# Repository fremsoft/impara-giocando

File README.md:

# impara-giocando

In questa directory verrà caricato tutto il materiale didattico che servirà per seguire meglio i laboratori di meccatronica «impara giocando»

La playlist completa è disponibile in abbonamento a questo link: [Laboratori di Meccatronica](https://www.youtube.com/playlist?list=PLxAafib4pWc7ZTqss_0A76ByotfsSOVeD)

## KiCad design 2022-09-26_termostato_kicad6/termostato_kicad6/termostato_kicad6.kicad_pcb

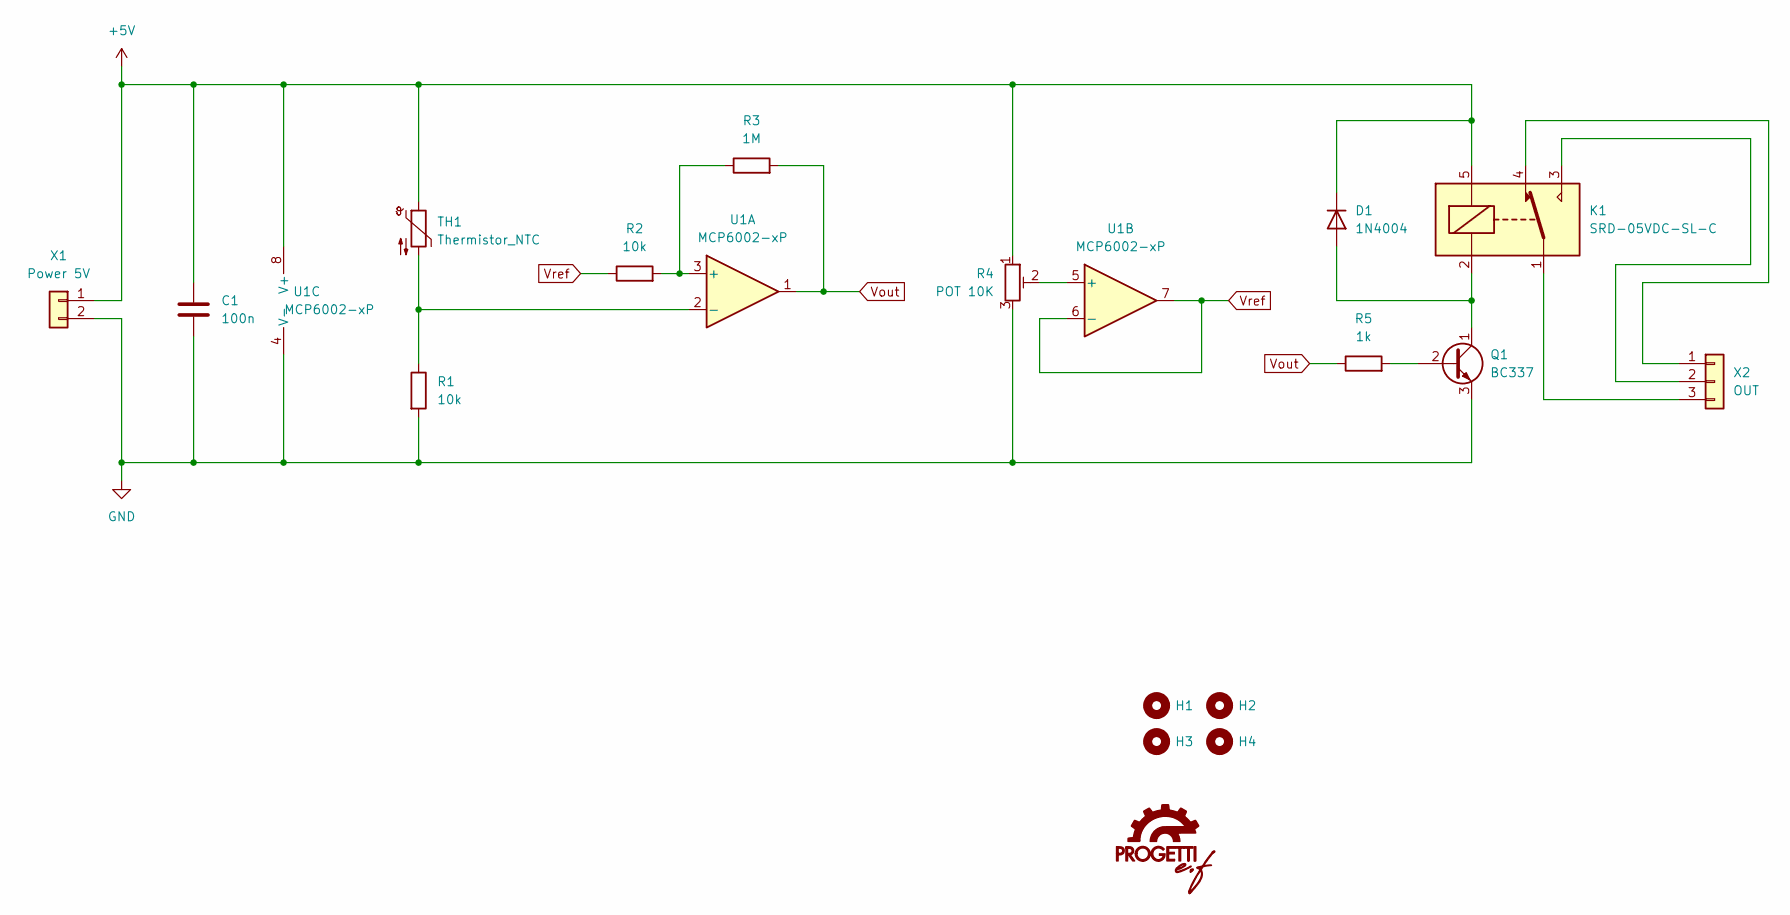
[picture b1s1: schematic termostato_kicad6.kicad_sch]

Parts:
C1: 100n; C_Disc_D7.5mm_W2.5mm_P5.00mm
D1: 1N4004; D_A-405_P10.16mm_Horizontal
H1, H2, H3, H4: MountingHole; MountingHole_4.3mm_M4
K1: SRD-05VDC-SL-C; Relay_SPDT_SANYOU_SRD_Series_Form_C
Q1: BC337; TO-92L_Inline_Wide
R1, R2: 10k; R_Axial_DIN0207_L6.3mm_D2.5mm_P10.16mm_Horizontal
R3: 1M; R_Axial_DIN0207_L6.3mm_D2.5mm_P10.16mm_Horizontal
R4: POT 10K; Potentiometer_Alps_RK163_Single_Horizontal
R5: 1k; R_Axial_DIN0207_L6.3mm_D2.5mm_P10.16mm_Horizontal
TH1: Thermistor_NTC; C_Rect_L4.6mm_W3.0mm_P2.50mm_MKS02_FKP02
U1: MCP6002-xP; DIP-8_W7.62mm_LongPads
X1: Power 5V; PhoenixContact_MSTBA_2,5_2-G-5,08_1x02_P5.08mm_Horizontal
X2: OUT; PhoenixContact_MSTBA_2,5_3-G-5,08_1x03_P5.08mm_Horizontal

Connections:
+5V: C1.1, D1.1 (K), K1.5, R4.1, TH1.1, U1.8 (V+), X1.1
GND: C1.2, Q1.3 (E), R1.2, R4.3, U1.4 (V-), X1.2
unnamed: D1.2 (A), K1.2, Q1.1 (C)
unnamed: K1.1, X2.3
unnamed: K1.3, X2.2
unnamed: K1.4, X2.1
unnamed: Q1.2 (B), R5.2
unnamed: R1.1, TH1.2, U1.2 (-)
unnamed: R2.2, R3.1, U1.3 (+)
unnamed: R4.2, U1.5 (+)
Vout: R3.2, R5.1, U1.1
Vref: R2.1, U1.6 (-), U1.7

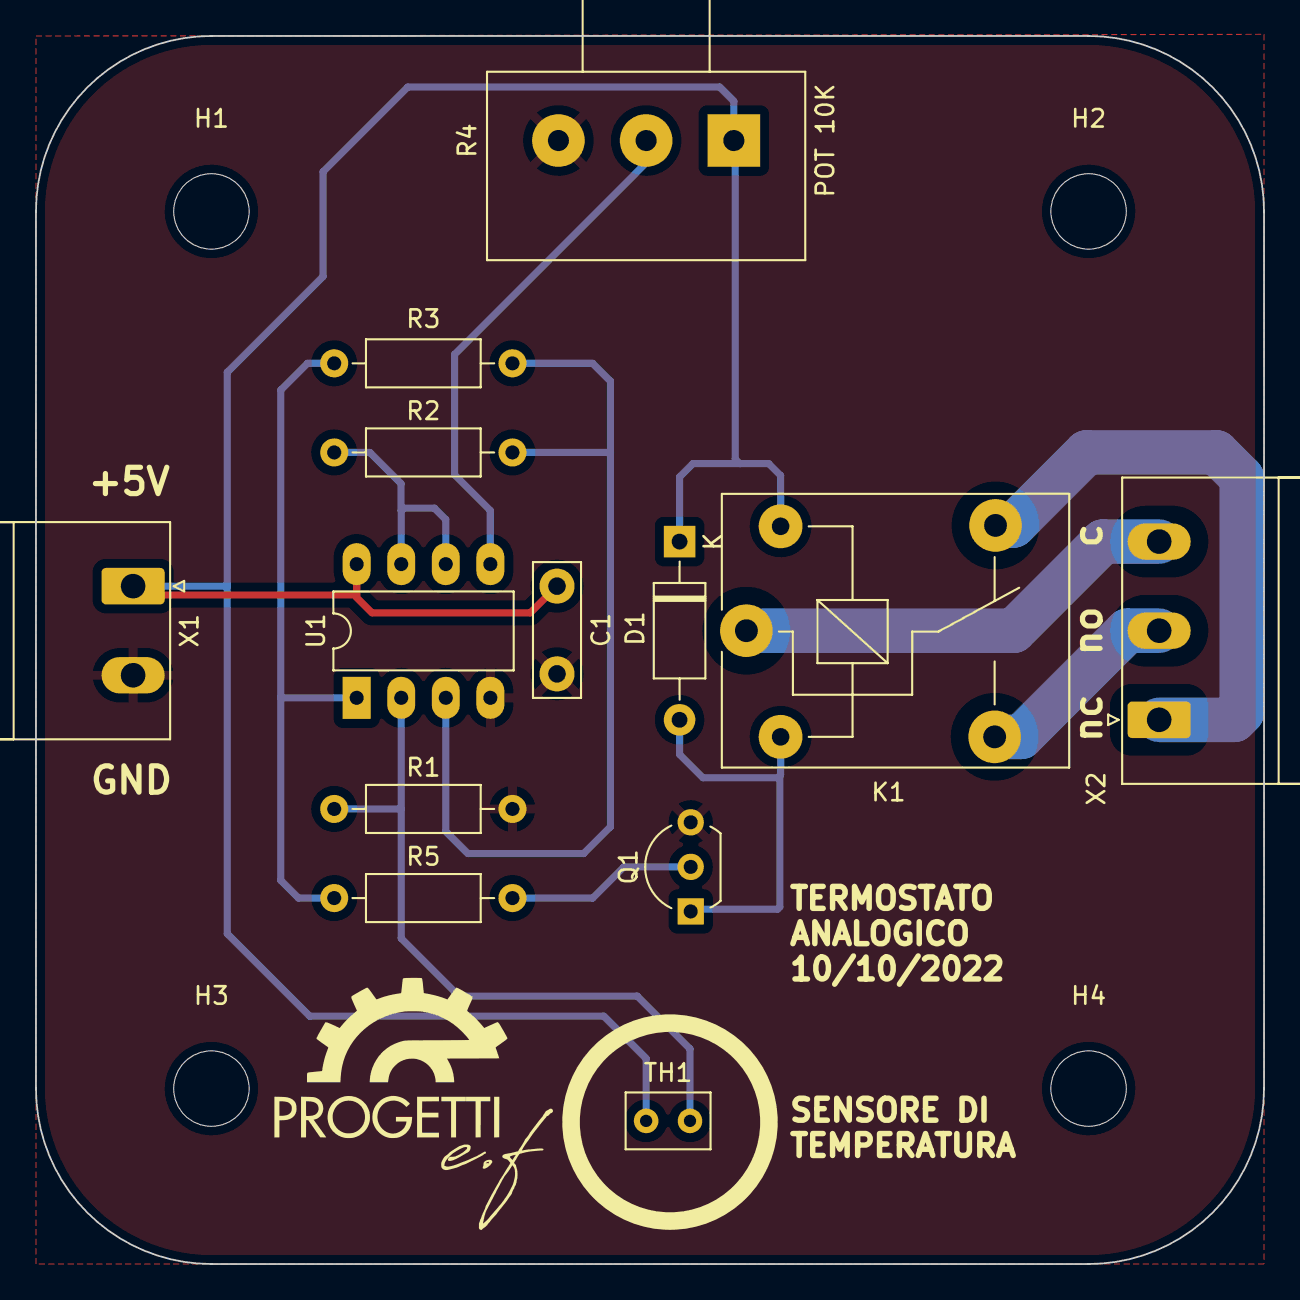
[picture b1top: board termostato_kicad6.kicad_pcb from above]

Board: 2 copper layers, 70.0 x 70.0 mm, 17 parts (0 on the bottom side), 12 nets.

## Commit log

2021-12-13 prima accensione arduino uno
2021-12-23 Jingle Bells
2022-01-17 Disegnare con oscilloscopio
2022-01-24 Lab 24-gen-2022
2022-01-31 Lab 31-01-2022
2022-02-07 Servomotore SG90
2022-02-14 Impara Giocando 14 febbraio
2022-02-22 Aggiunto link YouTube
2022-02-28 Laboratorio 28 febbraio 2022
    Esperienza sui motori stepper 28BYJ-48 a 5V
2022-03-01 Accessori
2022-03-10 solar tracker
2022-03-11 solar tracking
2022-03-14 sorgente esercizio
2022-03-21 porta seriale
2022-03-28 Porta seriale di Arduino e Json
2022-04-04 Lab Sonar HC-SR04
2022-04-08 Porta Seriale di Arduino UNO
2022-04-08 Sonar HC-SR04
2022-04-08 draft
2022-04-23 max7219
2022-04-25 Laboratorio del 25 aprile 2022
2022-05-02 2 maggio 2022
2022-05-09 gestione collisioni
2022-05-16 BUZZER
2022-05-23 23 maggio 2022
2022-05-30 LCD 1602 Grafica
2022-05-30 Grafica LCD1602
2022-06-13 termistore NTC
2022-06-20 DHT11
2022-07-18 Crepuscolare per irrigazione
2022-07-25 corretto tt
2022-07-25 Sketch completo
2022-08-01 display 7 segmenti
2022-08-08 display 7 segmenti 4 cifre
2022-09-12 telecomando infrarossi
2022-09-12 ACCENDE LED SU PIN 10
2022-09-19 Json Arduino
2022-09-26 KiCad6
2022-10-03 layout
2022-10-04 accoppiamento motore ruota
2022-10-04 STEP FILE
2022-10-10 GERBER
2022-11-07 Schema pdf
